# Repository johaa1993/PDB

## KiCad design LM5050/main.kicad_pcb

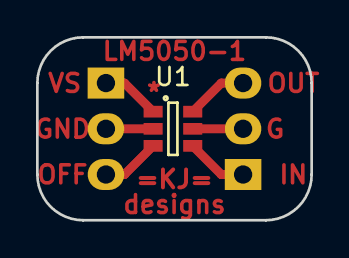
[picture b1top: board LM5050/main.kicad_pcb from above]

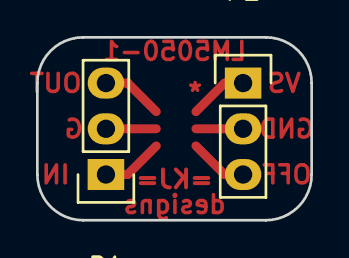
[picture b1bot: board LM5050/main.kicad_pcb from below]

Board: 2 copper layers, 15.2 x 10.2 mm, 3 parts (2 on the bottom side), 6 nets.

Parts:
P1, P2: CONN_01X03; Pin_Header_Straight_1x03
U1: LM5050; SOT-23-6

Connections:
unnamed: P1.1, U1.4
unnamed: P1.2, U1.5
unnamed: P1.3, U1.6
unnamed: P2.1, U1.1
unnamed: P2.2, U1.2
unnamed: P2.3, U1.3

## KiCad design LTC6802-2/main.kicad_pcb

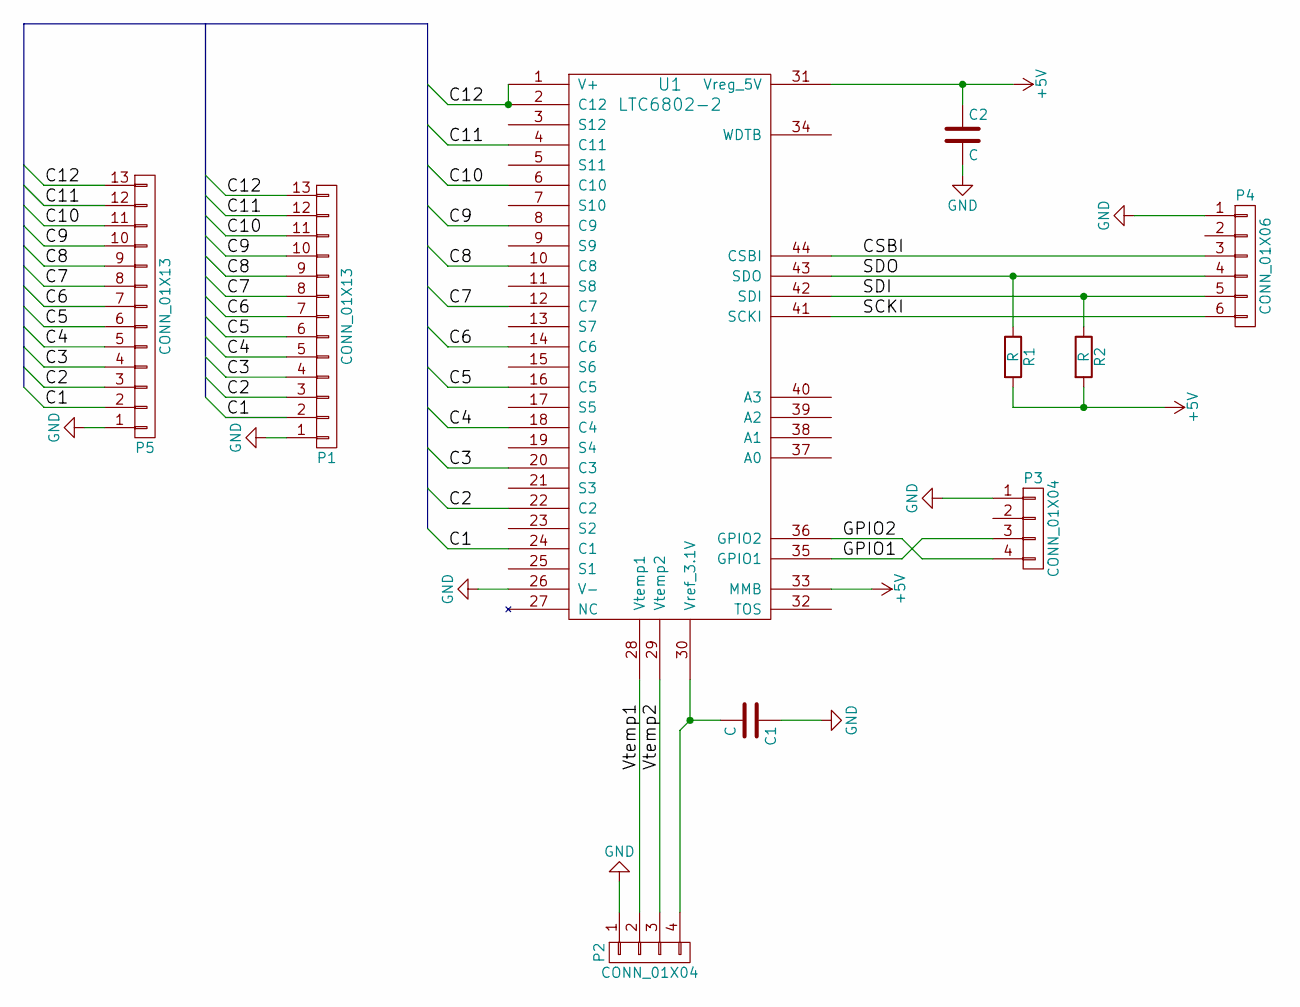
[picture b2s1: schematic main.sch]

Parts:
C1, C2: C; C_0805
P1, P5: CONN_01X13; Pin_Header_Straight_1x13
P2, P3: CONN_01X04; Pin_Header_Straight_1x04
P4: CONN_01X06; Pin_Header_Straight_1x06
R1, R2: R; R_0805
U1: LTC6802-2; SSOP-44

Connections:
+5V: C2.1, R1.2, R2.2, U1.31 (Vreg_5V), U1.33 (MMB)
/C1: P1.2, P5.2, U1.24 (C1)
/C2: P1.3, P5.3, U1.22 (C2)
/C3: P1.4, P5.4, U1.20 (C3)
/C4: P1.5, P5.5, U1.18 (C4)
/C5: P1.6, P5.6, U1.16 (C5)
/C6: P1.7, P5.7, U1.14 (C6)
/C7: P1.8, P5.8, U1.12 (C7)
/C8: P1.9, P5.9, U1.10 (C8)
/C9: P1.10, P5.10, U1.8 (C9)
/C10: P1.11, P5.11, U1.6 (C10)
/C11: P1.12, P5.12, U1.4 (C11)
/C12: P1.13, P5.13, U1.1 (V+), U1.2 (C12)
/CSBI: P4.3, U1.44 (CSBI)
/GPIO1: P3.3, U1.35 (GPIO1)
/GPIO2: P3.4, U1.36 (GPIO2)
/SCKI: P4.6, U1.41 (SCKI)
/SDI: P4.5, R2.1, U1.42 (SDI)
/SDO: P4.4, R1.1, U1.43 (SDO)
/Vtemp1: P2.2, U1.28 (Vtemp1)
/Vtemp2: P2.3, U1.29 (Vtemp2)
GND: C1.1, C2.2, P1.1, P2.1, P3.1, P4.1, P5.1, U1.26 (V-)
unnamed: C1.2, P2.4, U1.30 (Vref_3.1V)

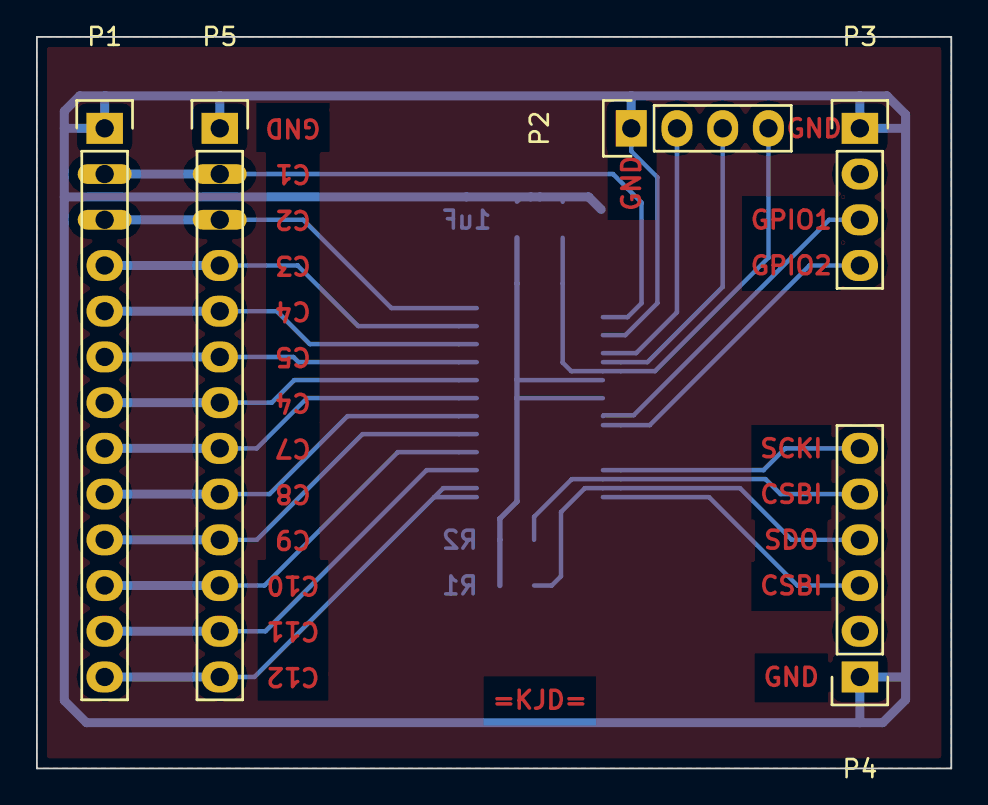
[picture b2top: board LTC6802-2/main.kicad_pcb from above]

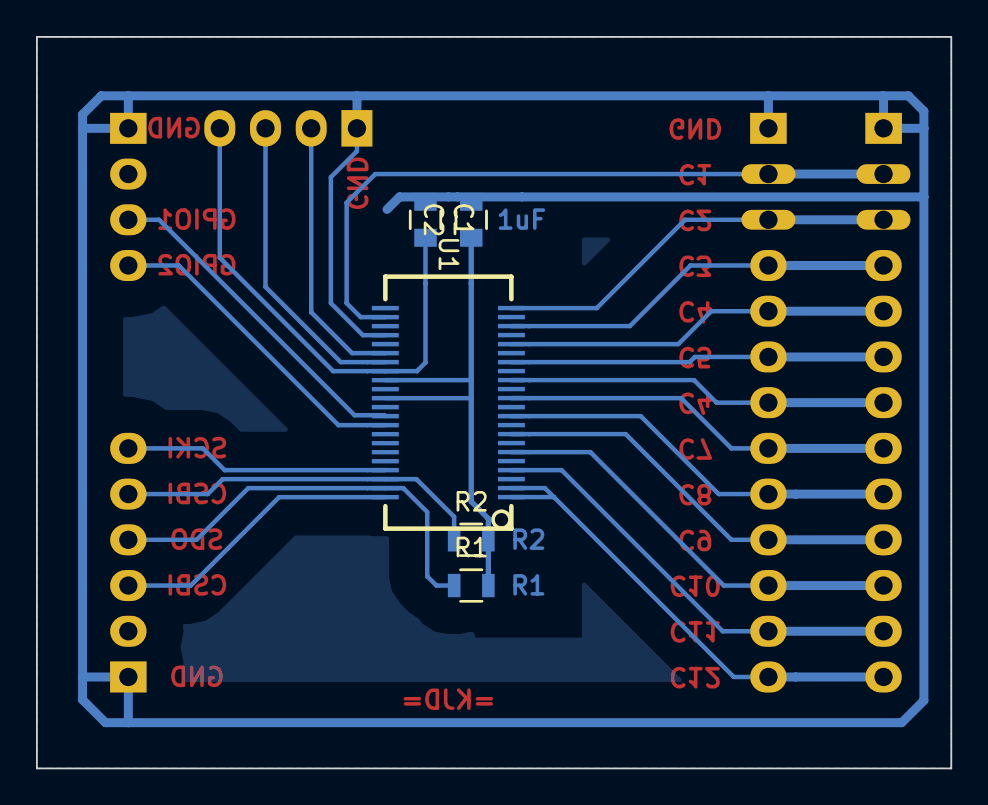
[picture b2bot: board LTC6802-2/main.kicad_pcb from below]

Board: 2 copper layers, 50.8 x 40.6 mm, 10 parts (5 on the bottom side), 23 nets.

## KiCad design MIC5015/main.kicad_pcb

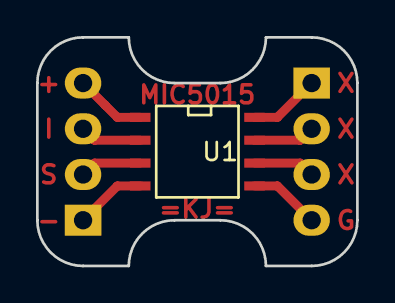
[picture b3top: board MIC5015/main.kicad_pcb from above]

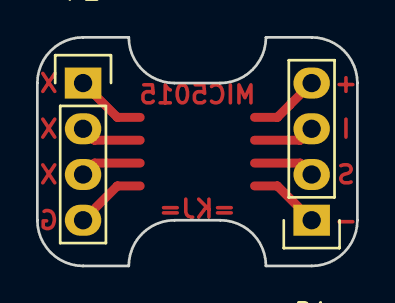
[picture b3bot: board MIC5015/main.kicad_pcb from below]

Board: 2 copper layers, 17.8 x 12.7 mm, 3 parts (2 on the bottom side), 8 nets.

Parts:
P1, P2: CONN_01X04; Pin_Header_Straight_1x04
U1: MIC5014; SOIC-8-N

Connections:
unnamed: P1.1, U1.4
unnamed: P1.2, U1.3
unnamed: P1.3, U1.2
unnamed: P1.4, U1.1
unnamed: P2.1, U1.8
unnamed: P2.2, U1.7
unnamed: P2.3, U1.6
unnamed: P2.4, U1.5

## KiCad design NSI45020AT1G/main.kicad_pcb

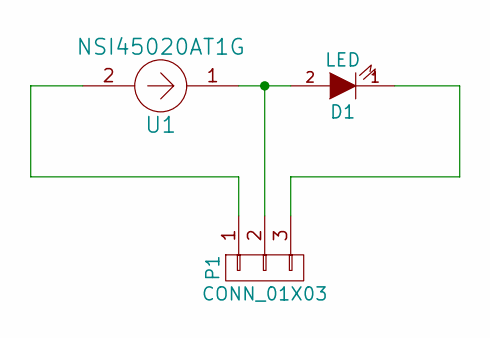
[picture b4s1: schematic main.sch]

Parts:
D1: LED; LED_0805
P1: CONN_01X03; Pin_Header_Angled_1x03
U1: NSI45020AT1G; SOD-123

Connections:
unnamed: D1.1 (K), P1.3
unnamed: D1.2 (A), P1.2, U1.1
unnamed: P1.1, U1.2

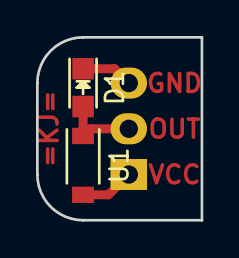
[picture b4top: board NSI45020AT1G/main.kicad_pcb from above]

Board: 2 copper layers, 9.1 x 10.2 mm, 3 parts (1 on the bottom side), 3 nets.

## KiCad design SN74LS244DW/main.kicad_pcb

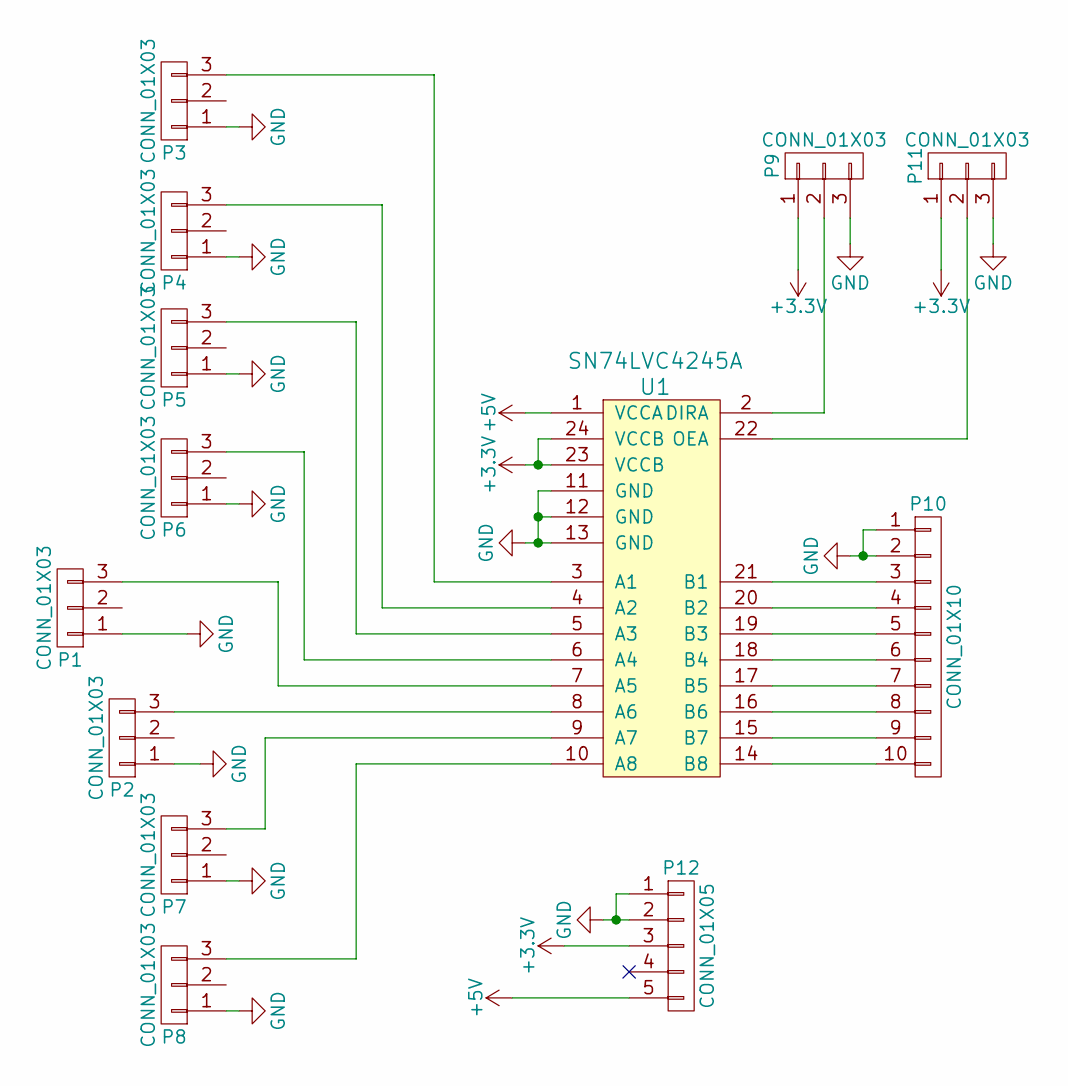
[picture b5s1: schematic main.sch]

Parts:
P1, P2, P3, P4, P5, P6, P7, P8, P9, P11: CONN_01X03; Pin_Header_Straight_1x03
P10: CONN_01X10; Pin_Header_Straight_1x10
P12: CONN_01X05; Pin_Header_Straight_1x05
U1: SN74LVC4245A; SOIC-24W_7.5x15.4mm_Pitch1.27mm

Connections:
+3V3: P9.1, P11.1, P12.3, U1.23 (VCCB), U1.24 (VCCB)
+5V: P12.5, U1.1 (VCCA)
GND: P1.1, P2.1, P3.1, P4.1, P5.1, P6.1, P7.1, P8.1, P9.3, P10.1, P10.2, P11.3, P12.1, P12.2, U1.11 (GND), U1.12 (GND), U1.13 (GND)
unnamed: P1.3, U1.7 (A5)
unnamed: P2.3, U1.8 (A6)
unnamed: P3.3, U1.3 (A1)
unnamed: P4.3, U1.4 (A2)
unnamed: P5.3, U1.5 (A3)
unnamed: P6.3, U1.6 (A4)
unnamed: P7.3, U1.9 (A7)
unnamed: P8.3, U1.10 (A8)
unnamed: P9.2, U1.2 (DIRA)
unnamed: P10.3, U1.21 (B1)
unnamed: P10.4, U1.20 (B2)
unnamed: P10.5, U1.19 (B3)
unnamed: P10.6, U1.18 (B4)
unnamed: P10.7, U1.17 (B5)
unnamed: P10.8, U1.16 (B6)
unnamed: P10.9, U1.15 (B7)
unnamed: P10.10, U1.14 (B8)
unnamed: P11.2, U1.22 (OEA)

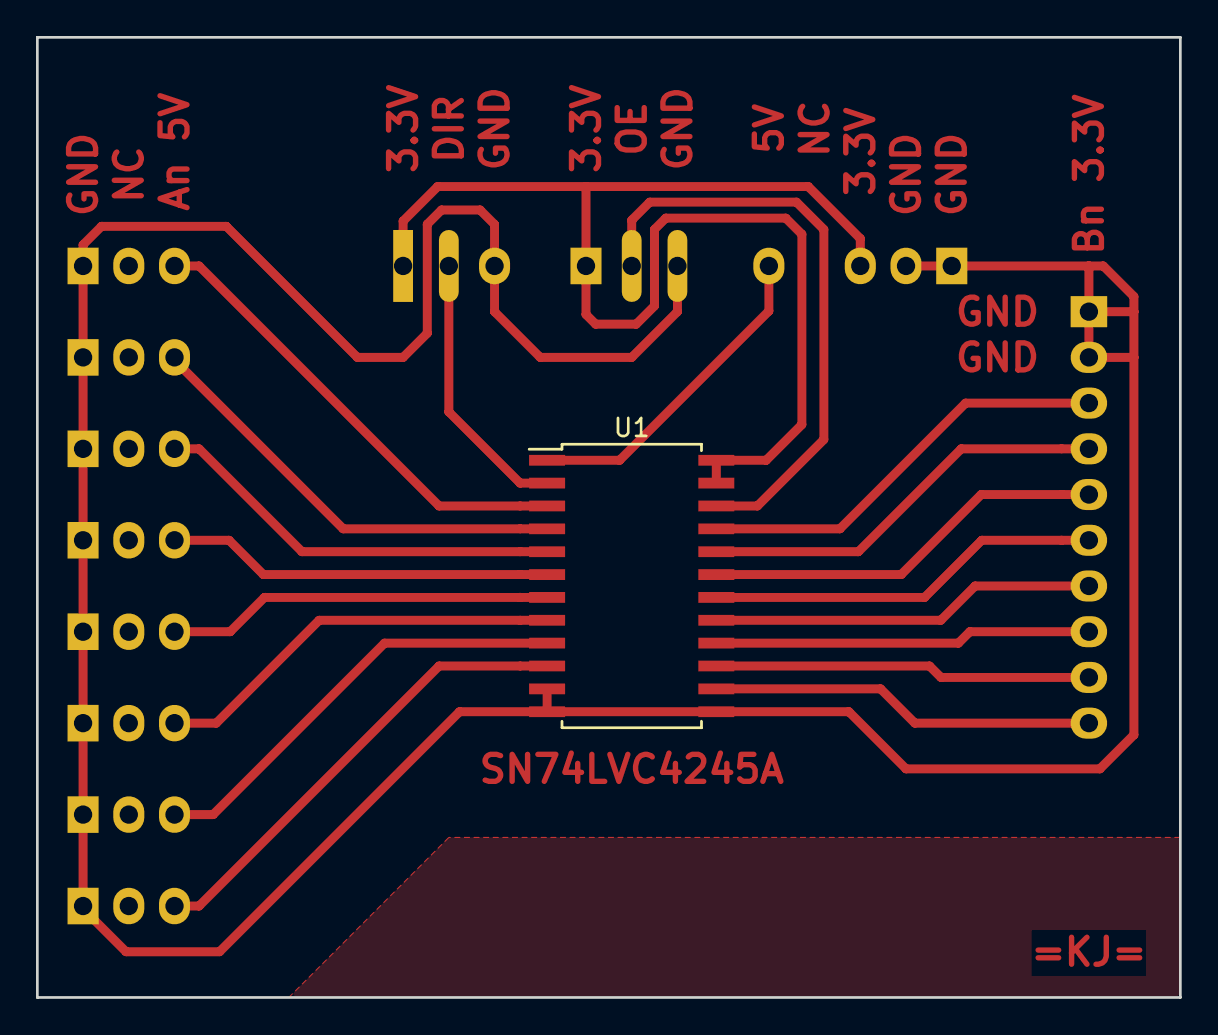
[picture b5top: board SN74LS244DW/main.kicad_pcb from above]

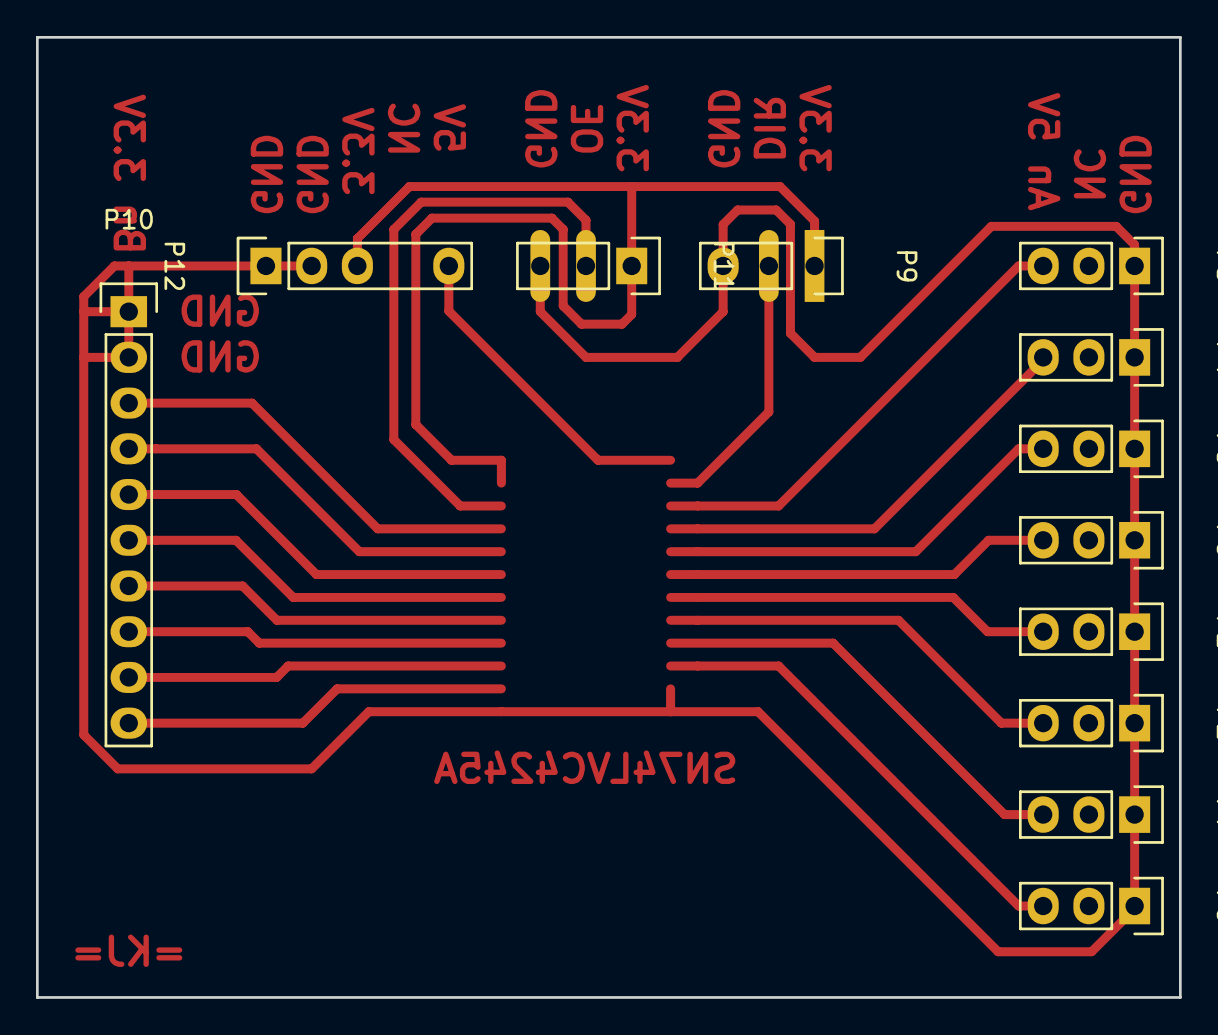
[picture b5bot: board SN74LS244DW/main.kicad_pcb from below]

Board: 2 copper layers, 63.5 x 53.3 mm, 13 parts (12 on the bottom side), 21 nets.

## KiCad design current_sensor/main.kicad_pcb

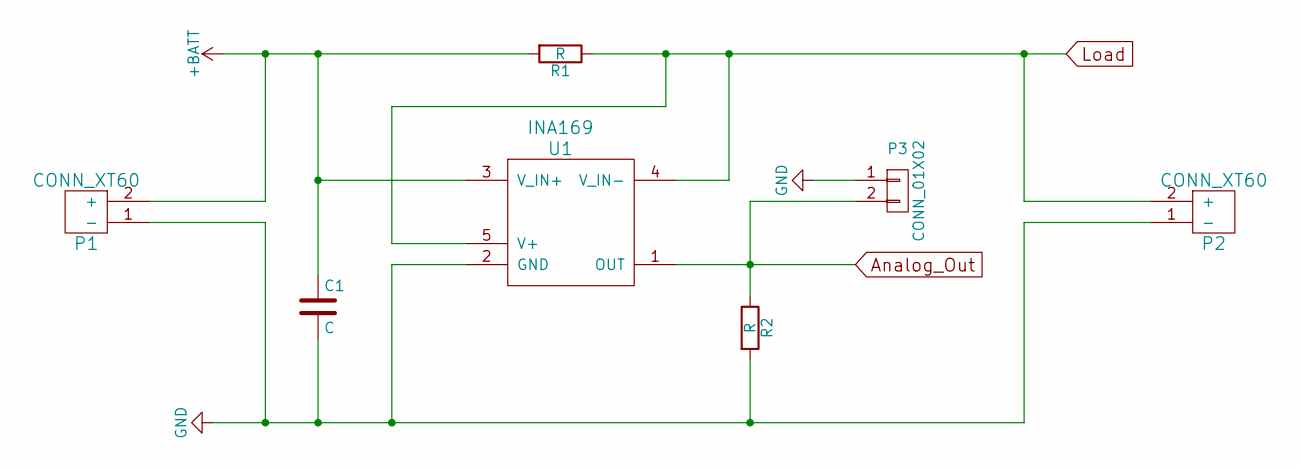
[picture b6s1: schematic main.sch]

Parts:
C1: C; C_0805_HandSoldering
P1, P2: CONN_XT60; XT60
P3: CONN_01X02; Pin_Header_Straight_1x03
R1: R; SMD_1052_Metric
R2: R; R_0805_HandSoldering
U1: INA169; SOT-23-5

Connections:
+BATT: C1.1, P1.2 (+), R1.2, U1.3 (V_IN+)
Analog_Out: P3.2, R2.1, U1.1 (OUT)
GND: C1.2, P1.1 (-), P2.1 (-), P3.1, R2.2, U1.2 (GND)
Load: P2.2 (+), R1.1, U1.4 (V_IN-), U1.5 (V+)

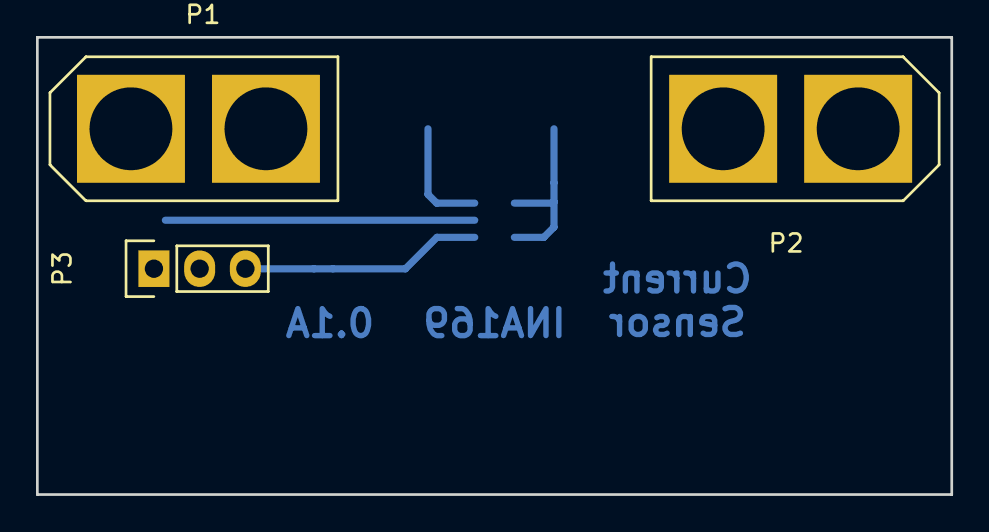
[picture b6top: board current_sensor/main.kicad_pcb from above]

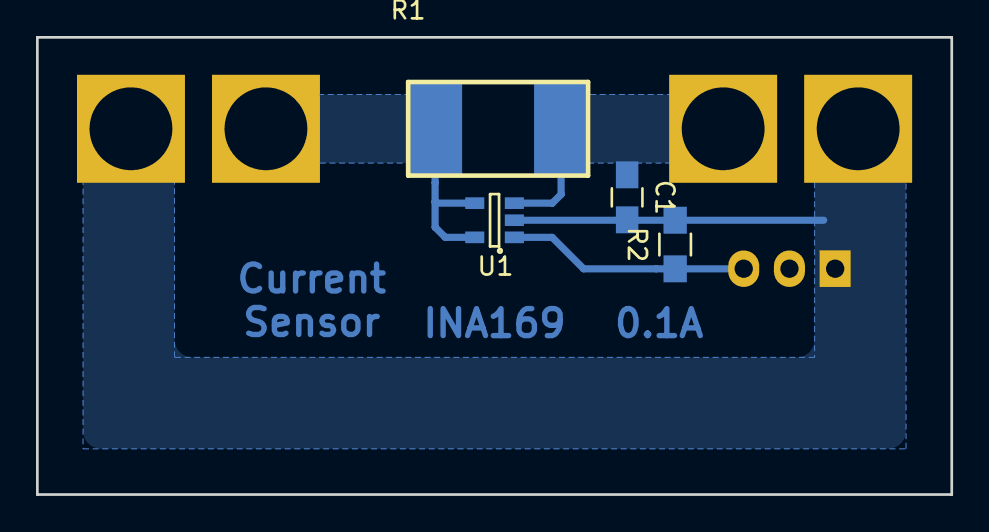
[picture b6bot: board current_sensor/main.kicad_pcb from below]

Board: 2 copper layers, 50.8 x 25.4 mm, 7 parts (4 on the bottom side), 4 nets.

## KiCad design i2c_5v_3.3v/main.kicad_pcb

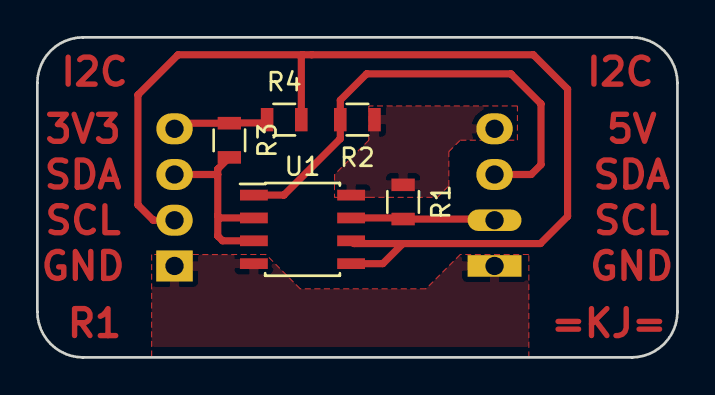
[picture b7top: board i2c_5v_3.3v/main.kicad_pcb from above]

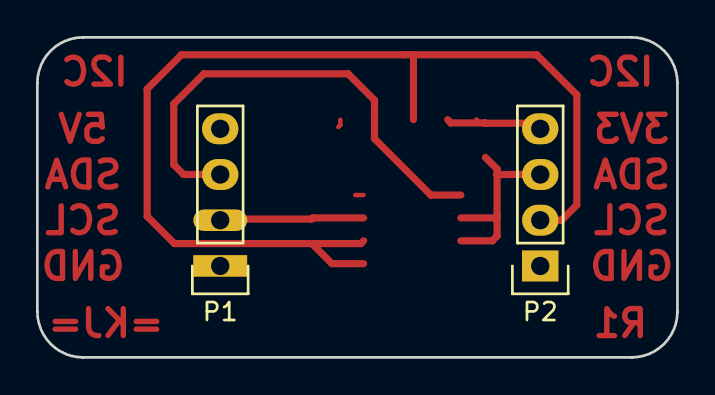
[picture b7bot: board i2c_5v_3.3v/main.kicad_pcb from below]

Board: 2 copper layers, 35.6 x 17.8 mm, 7 parts (2 on the bottom side), 7 nets.

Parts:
P1, P2: CONN_01X04; Pin_Header_Straight_1x04
R1, R2, R3, R4: 1k; R_0805
U1: P82B96; SOIC-8_3.9x4.9mm_Pitch1.27mm

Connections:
+3V3: P2.4, R3.1, R4.1
+5V: P1.4, R1.1, R2.1, U1.8
/SCL0: P1.2, R1.2, U1.7
/SCL1: P2.2, R4.2, U1.5, U1.6
/SDA0: P1.3, R2.2, U1.1
/SDA1: P2.3, R3.2, U1.2, U1.3
GND: P1.1, P2.1, U1.4
